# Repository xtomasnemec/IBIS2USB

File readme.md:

# IBIS to USB Converter

This project is a hardware solution for communicating with miscelaneous IBIS devices (BUSE BS210 etc.)

## Features

- Converts IBIS protocol to USB (virtual COM port)
- Mini USB
- Open hardware design (schematics and PCB in KiCad)

## Getting Started

1. Open the schematic and PCB files in KiCad.
2. Manufacture the PCB and assemble the components as specified.
3. Connect the IBIS and USB.
4. Use PuTTY to comunicate (1200 bit/s, 7 bits, even parity, 2 stop bits) or IBIS-Wagenbus Utility

## License

This project is open-source. See the LICENSE file for details.

## Credits

Developed by xtomasnemec.
Original IBIS to RS232 converter [here](https://jachyhm.cz/ois/Schemata/IBIS-COM_kompletni_schema.jpg).

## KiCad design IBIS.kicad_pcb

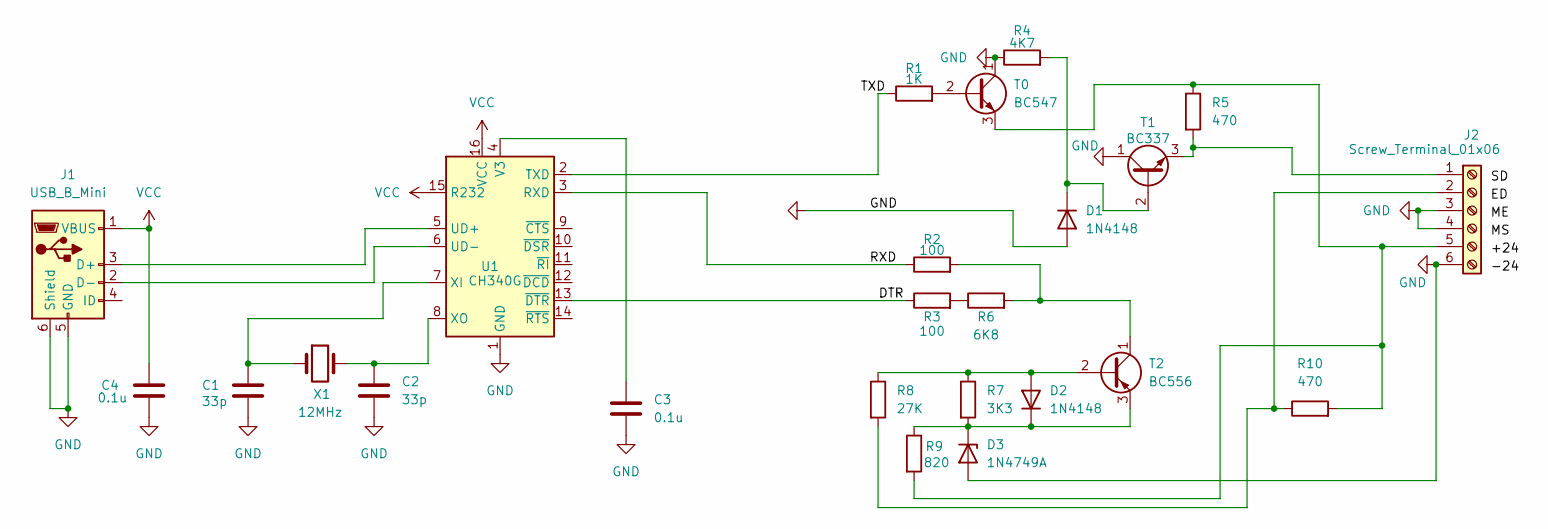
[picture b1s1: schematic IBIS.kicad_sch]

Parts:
C1, C2: 33p; C_Disc_D7.5mm_W5.0mm_P5.00mm
C3, C4: 0.1u; C_Disc_D7.5mm_W5.0mm_P5.00mm
D1, D2: 1N4148; D_DO-35_SOD27_P10.16mm_Horizontal
D3: 1N4749A; D_DO-41_SOD81_P10.16mm_Horizontal
J1: USB_B_Mini; USB_Mini-B_Wuerth_65100516121_Horizontal
J2: Screw_Terminal_01x06; TerminalBlock_WAGO_233-506_2x06_P2.54mm
R1: 1K; R_Axial_DIN0207_L6.3mm_D2.5mm_P10.16mm_Horizontal
R2, R3: 100; R_Axial_DIN0207_L6.3mm_D2.5mm_P10.16mm_Horizontal
R4: 4K7; R_Axial_DIN0207_L6.3mm_D2.5mm_P10.16mm_Horizontal
R5, R10: 470; R_Axial_DIN0207_L6.3mm_D2.5mm_P10.16mm_Horizontal
R6: 6K8; R_Axial_DIN0207_L6.3mm_D2.5mm_P10.16mm_Horizontal
R7: 3K3; R_Axial_DIN0207_L6.3mm_D2.5mm_P10.16mm_Horizontal
R8: 27K; R_Axial_DIN0207_L6.3mm_D2.5mm_P10.16mm_Horizontal
R9: 820; R_Axial_DIN0207_L6.3mm_D2.5mm_P10.16mm_Horizontal
T0: BC547; TO-92_Inline
T1: BC337; TO-92_Inline
T2: BC556; TO-92_Inline
U1: CH340G; SOIC-16_3.9x9.9mm_P1.27mm
X1: 12MHz; Crystal_HC49-4H_Vertical

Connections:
/DTR: R3.1, U1.13 (~DTR)
/RXD: R2.1, U1.3 (RXD)
GND: C1.2, C2.2, C3.2, C4.2, D1.2 (A), D3.2 (A), J1.5 (GND), J1.6 (Shield), J2.3, J2.4, J2.6, R4.1, T0.1 (C), T1.1 (C), U1.1 (GND)
unnamed: D1.1 (K), R4.2, T1.2 (B)
unnamed: D2.2 (A), R7.1, R8.1, T2.2 (B)
unnamed: D2.1 (K), D3.1 (K), R7.2, R9.1, T2.3 (E)
unnamed: J1.3 (D+), U1.5 (UD+)
unnamed: J1.2 (D-), U1.6 (UD-)
unnamed: J2.1, R5.2, T1.3 (E)
unnamed: J2.2, R8.2, R10.1
unnamed: J2.5, R5.1, R9.2, R10.2, T0.3 (E)
unnamed: R3.2, R6.1
unnamed: R1.2, T0.2 (B)
unnamed: R2.2, R6.2, T2.1 (C)
unnamed: R1.1, U1.2 (TXD)
unnamed: C3.1, U1.4 (V3)
unnamed: C1.1, U1.7 (XI), X1.1
unnamed: C2.1, U1.8 (XO), X1.2
VCC: C4.1, J1.1 (VBUS), U1.15 (R232), U1.16 (VCC)

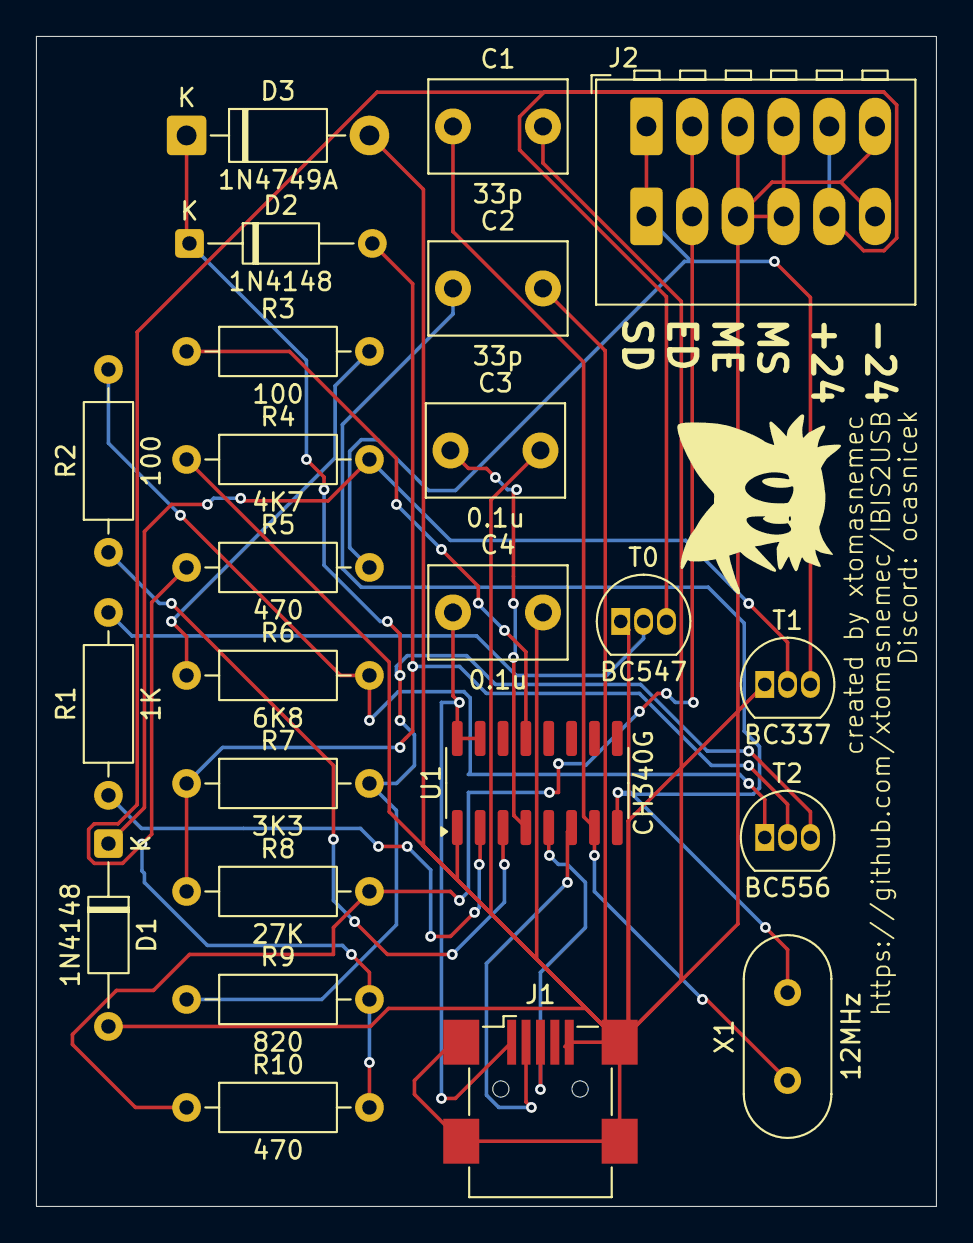
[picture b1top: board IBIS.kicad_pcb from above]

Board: 2 copper layers, 50.0 x 65.0 mm, 24 parts (0 on the bottom side), 19 nets.

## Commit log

2025-06-01 Full schematic only
2025-06-01 PCB design
